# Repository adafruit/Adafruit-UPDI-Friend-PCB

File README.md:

## Adafruit UPDI Friend USB Serial UPDI Programmer PCB

<a href="http://www.adafruit.com/products/5879"><br/>
Click here to purchase one from the Adafruit shop</a>

PCB files for the Adafruit UPDI Friend USB Serial UPDI Programmer. 

Format is EagleCAD schematic and board layout
* https://www.adafruit.com/product/5879

### Description

UPDI stands for Unified Program and Debug Interface, but this board is so smol and cute that we will call it the Unusually Playful Device Interfacer and pat its head when it does a good job. It's designed to make programming modern ATtiny chips very easy because it has 3V or 5V power and logic select, power and transmit indicator LEDs, and a quick cable for poking into a breadboard.

We have been working a lot with ATtiny816, ATtiny817 and ATtiny1616 chips lately, as for our seesaw boards. And we're often needing to program them with a CP2102-based breakout with a 1K resistor soldered between the RX and TX pins. But we were hankering for a nicer programmer!

This UPDI Friend makes programming such chips very easy:

* Select between 3V or 5V power and logic - the 3V regulator can source up to 500mA so it can run even big projects. 
* CH340E USB Serial converter chip with cross-platform drivers
* 1K Loop-back Resistor between RX and TX
* USB Type C for data and power connection to any computer
* JST SH cable included for quick plugging into a breadboard - you can get another JST SH 3-pin cable with sockets or with pin header here.
* 0.1" spaced breakout holes for custom connections.
* Green power OK LED
* Red serial activity LED
* Inspired by this [open-source hardware design](https://github.com/wagiminator/AVR-Programmer/tree/master/SerialUPDI_Programmer) from [Stefan Wagner](https://github.com/wagiminator)!

We use Arduino IDE with the megaTinyCore board support package installed, simply select "Serial UPDI" as the programmer type, we use 230Kbps but 56Kbps is also good.

### License

Adafruit invests time and resources providing this open source design, please support Adafruit and open-source hardware by purchasing products from [Adafruit](https://www.adafruit.com)!

Designed by Limor Fried/Ladyada for Adafruit Industries.

Creative Commons Attribution/Share-Alike, all text above must be included in any redistribution. 
See license.txt for additional details.

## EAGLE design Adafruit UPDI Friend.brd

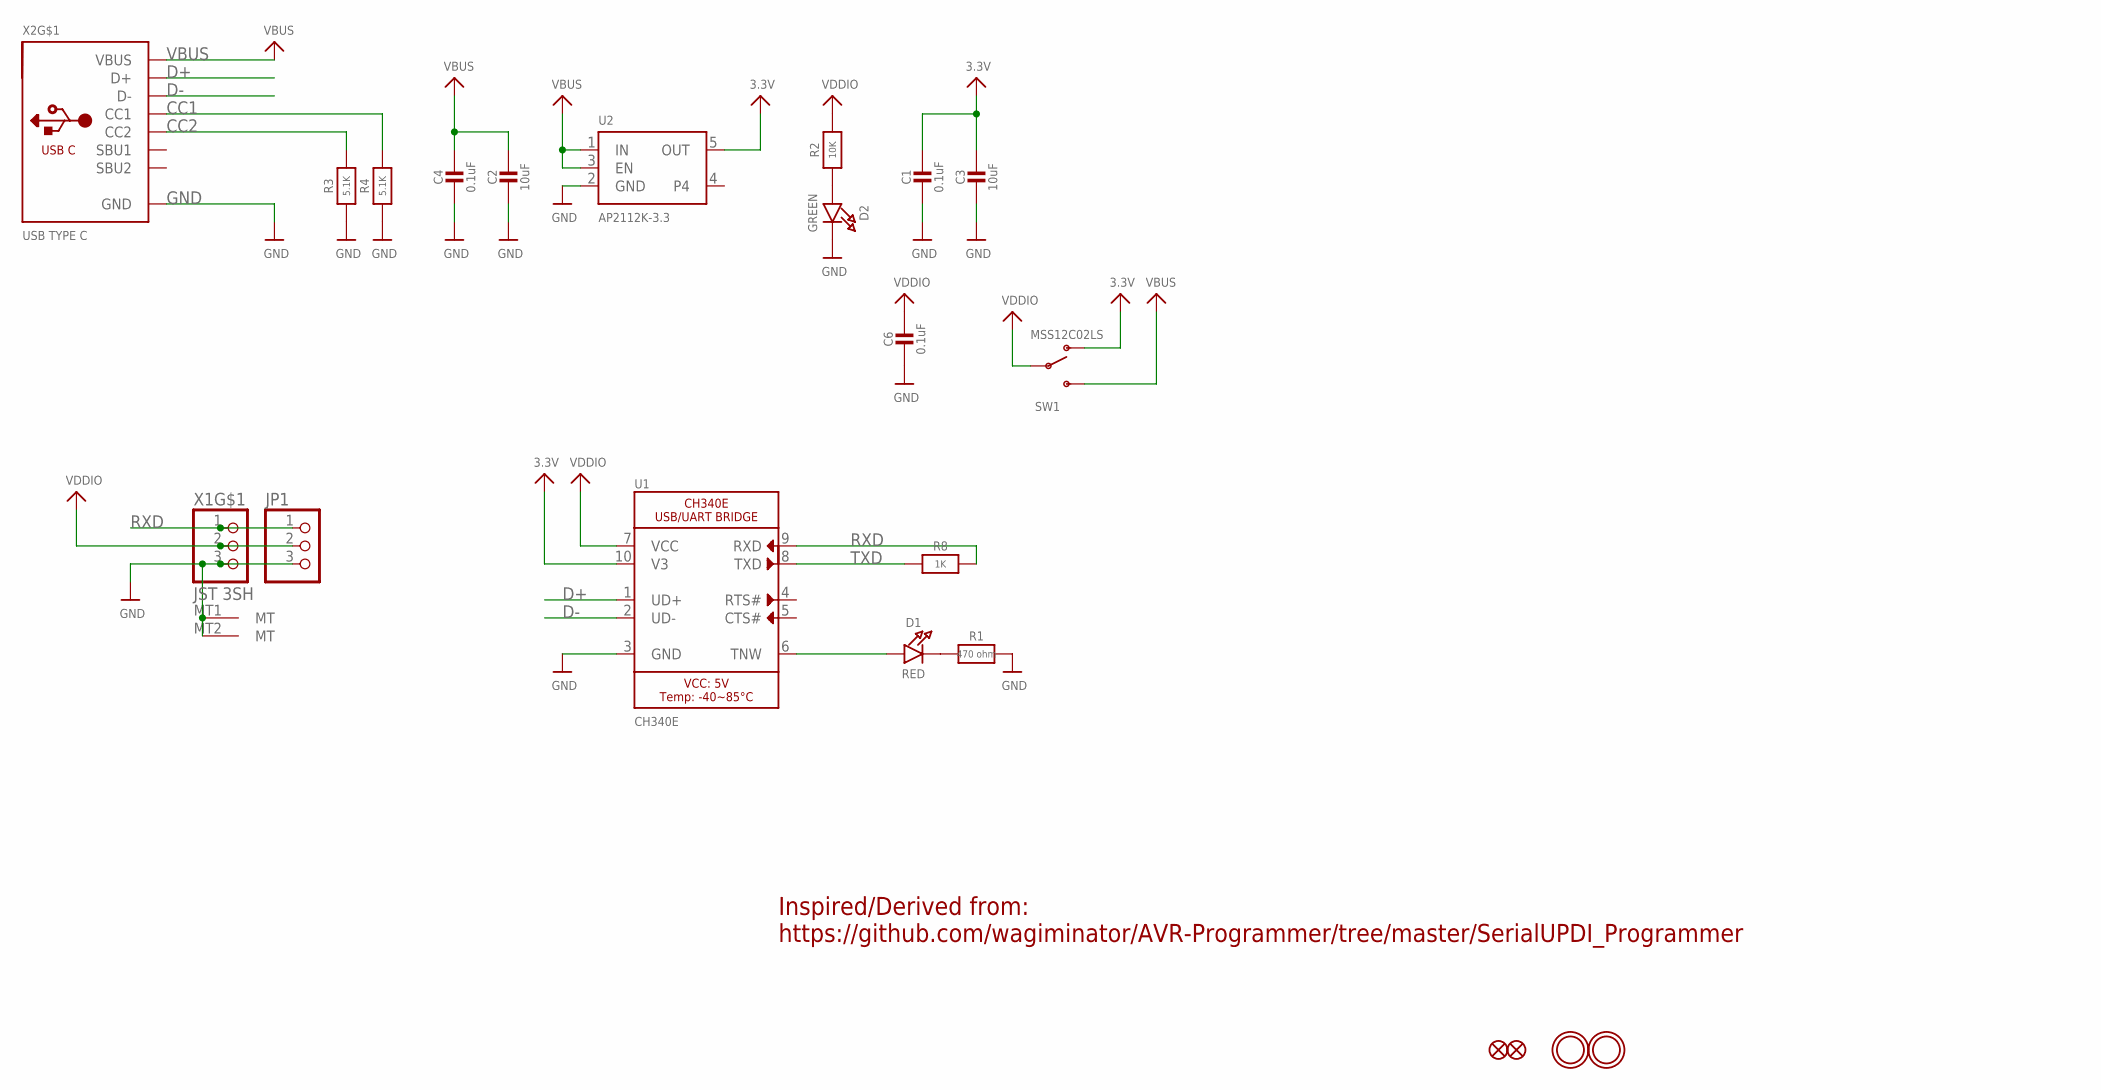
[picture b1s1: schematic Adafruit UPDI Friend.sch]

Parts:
C1, C4, C6: 0.1uF; 0603-NO
C2, C3: 10uF; 0805-NO
D1: RED; CHIPLED_0603_NOOUTLINE
D2: GREEN; CHIPLED_0603_NOOUTLINE
FID1, FID2: FIDUCIAL_1MM
JP1: HEADER-1X376MIL; 1X03_ROUND_76
R1: 470 ohm; 0603-NO
R2: 10K; 0603-NO
R3, R4: 5.1K; 0603-NO
R8: 1K; 0603-NO
SW1: MSS12C02LS; SPDT_SMT_SSSS811101
U1: CH340E; MSOP10
U2: AP2112K-3.3; SOT23-5; JLC_ROTATION 0
U$18, U$19: MOUNTINGHOLE2.0; MOUNTINGHOLE_2.0_PLATED
X1: JST 3SH; JST_SH3
X2: USB TYPE C; USB_C_CUSB31-CFM2AX-01-X

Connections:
3.3V: C1.1, C3.1, SW1.A (O), U1.10 (V3), U2.5 (OUT)
CC1: R4.2, X2.A5 (CC1)
CC2: R3.2, X2.B5 (CC2)
D+: U1.1 (UD+), X2.A6 (D+), X2.B6 (D+)
D-: U1.2 (UD-), X2.A7 (D-), X2.B7 (D-)
GND: C1.2, C2.2, C3.2, C4.2, C6.2, D2.C, JP1.3, R1.2, R3.1, R4.1, U1.3 (GND), U2.2 (GND), X1.3, X1.MT1 (MT), X1.MT2 (MT), X2.A1B12 (GND), X2.B1A12 (GND)
unnamed: D1.C, R1.1
unnamed: D1.A, U1.6 (TNW)
unnamed: D2.A, R2.1
RXD: JP1.1, R8.2, U1.9 (RXD), X1.1
TXD: R8.1, U1.8 (TXD)
VBUS: C2.1, C4.1, SW1.C (S), U2.1 (IN), U2.3 (EN), X2.A4B9 (VBUS), X2.B4A9 (VBUS)
VDDIO: C6.1, JP1.2, R2.2, SW1.B, U1.7 (VCC), X1.2

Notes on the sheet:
Inspired/Derived from: https://github.com/wagiminator/AVR-Programmer/tree/master/SerialUPDI_Programmer

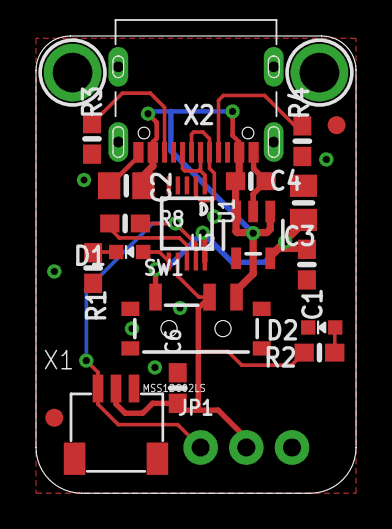
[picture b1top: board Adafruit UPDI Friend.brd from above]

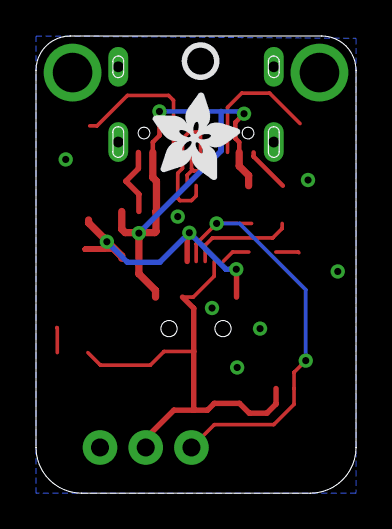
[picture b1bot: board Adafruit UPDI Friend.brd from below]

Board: 2 copper layers, 17.8 x 25.4 mm, 37 parts (7 on the bottom side), 13 nets.

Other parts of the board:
PLABEL0: PLABEL0
PLABEL1: PLABEL1
PLABEL2: PLABEL2
PLABEL3: PLABEL3
PLABEL4: PLABEL4
PLABEL5: PLABEL5
PLABEL6: PLABEL6
PLABEL7: PLABEL7
PLABEL8: PLABEL8
PLABEL9: PLABEL9
PLABEL10: PLABEL10
PLABEL11: PLABEL11
PLABEL12: PLABEL12
U$9: ADAFRUIT_5MM
U$17: PCBFEAT-REV-040

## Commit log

2024-01-26 cookiecutter output

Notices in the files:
parts and their libraries:
microbuilder: This work is placed in the public domain, and may be freely used for commercial and non-commercial work with the following conditions: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
